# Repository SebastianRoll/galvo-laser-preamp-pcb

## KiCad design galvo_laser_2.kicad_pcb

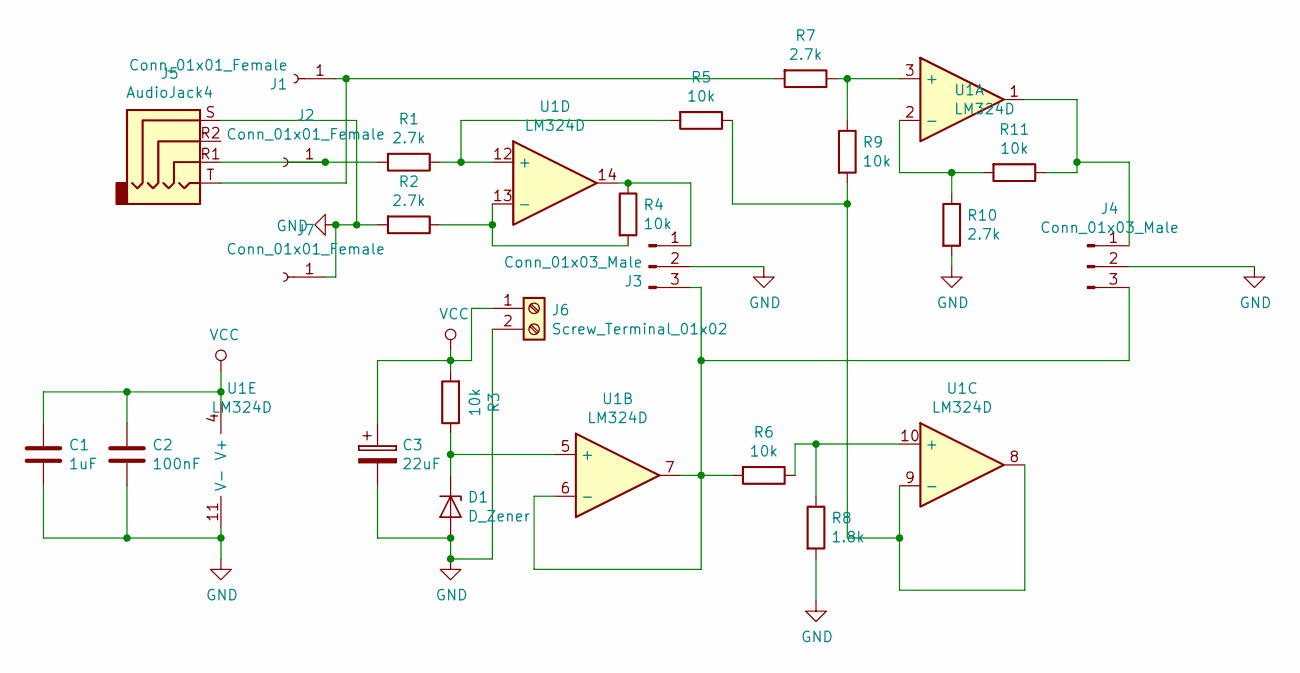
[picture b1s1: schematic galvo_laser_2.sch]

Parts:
C1: 1uF; C_0603_1608Metric
C2: 100nF; C_0805_2012Metric
C3: 22uF; CP_EIA-3216-18_Kemet-A
D1: D_Zener; D_SOD-123
J1, J2, J7: Conn_01x01_Female; PinHeader_1x01_P2.54mm_Vertical
J3, J4: Conn_01x03_Male; JST_XH_B03B-XH-A_1x03_P2.50mm_Vertical
J5: AudioJack4; Jack_3.5mm_PJ320D_Horizontal
J6: Screw_Terminal_01x02; TerminalBlock_Phoenix_MKDS-1,5-2_1x02_P5.00mm_Horizontal
R1, R2, R7, R10: 2.7k; R_0603_1608Metric
R3, R4, R5, R6, R9, R11: 10k; R_0603_1608Metric
R8: 1.8k; R_0603_1608Metric
U1: LM324D; SOIC-14_3.9x8.7mm_P1.27mm

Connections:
GND: C1.2, C2.2, C3.2, D1.2 (A), J3.2, J4.2, J5.S, J6.2, J7.1, R2.2, R8.2, R10.2, U1.11 (V-)
unnamed: D1.1 (K), R3.1, U1.5 (+)
unnamed: J1.1, J5.T, R7.2
unnamed: J2.1, J5.R1, R1.2
unnamed: J3.1, R4.1, U1.14
unnamed: J3.3, J4.3, R6.2, U1.6 (-), U1.7
unnamed: J4.1, R11.1, U1.1
unnamed: R1.1, R5.2, U1.12 (+)
unnamed: R2.1, R4.2, U1.13 (-)
unnamed: R5.1, R9.2, U1.8, U1.9 (-)
unnamed: R6.1, R8.1, U1.10 (+)
unnamed: R7.1, R9.1, U1.3 (+)
unnamed: R10.1, R11.2, U1.2 (-)
VCC: C1.1, C2.1, C3.1, J6.1, R3.2, U1.4 (V+)

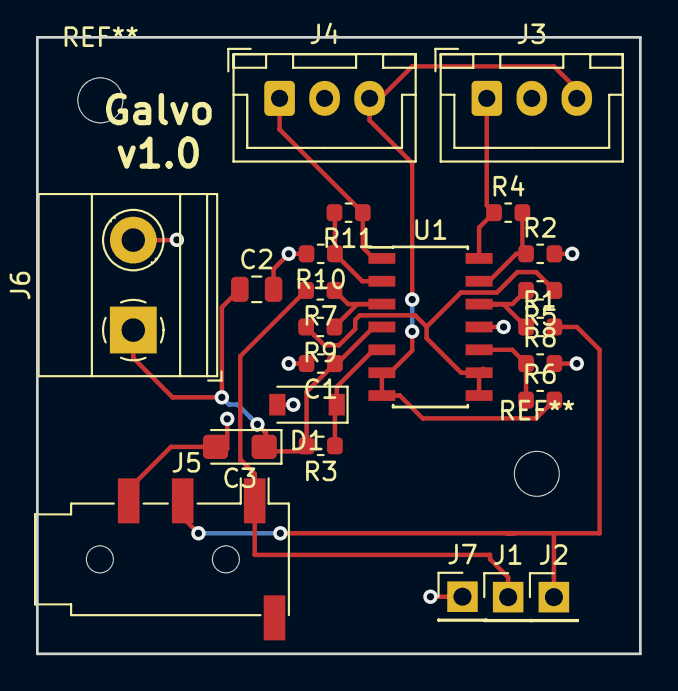
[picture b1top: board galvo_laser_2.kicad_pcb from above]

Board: 2 copper layers, 33.5 x 34.2 mm, 23 parts (0 on the bottom side), 14 nets.

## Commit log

2019-02-12 Add readme
2019-03-27 Add resistor values
2019-03-27 import netlist
2019-04-01 Connect screw terminal to ground
2019-04-01 Add ground connector for microcontroller
